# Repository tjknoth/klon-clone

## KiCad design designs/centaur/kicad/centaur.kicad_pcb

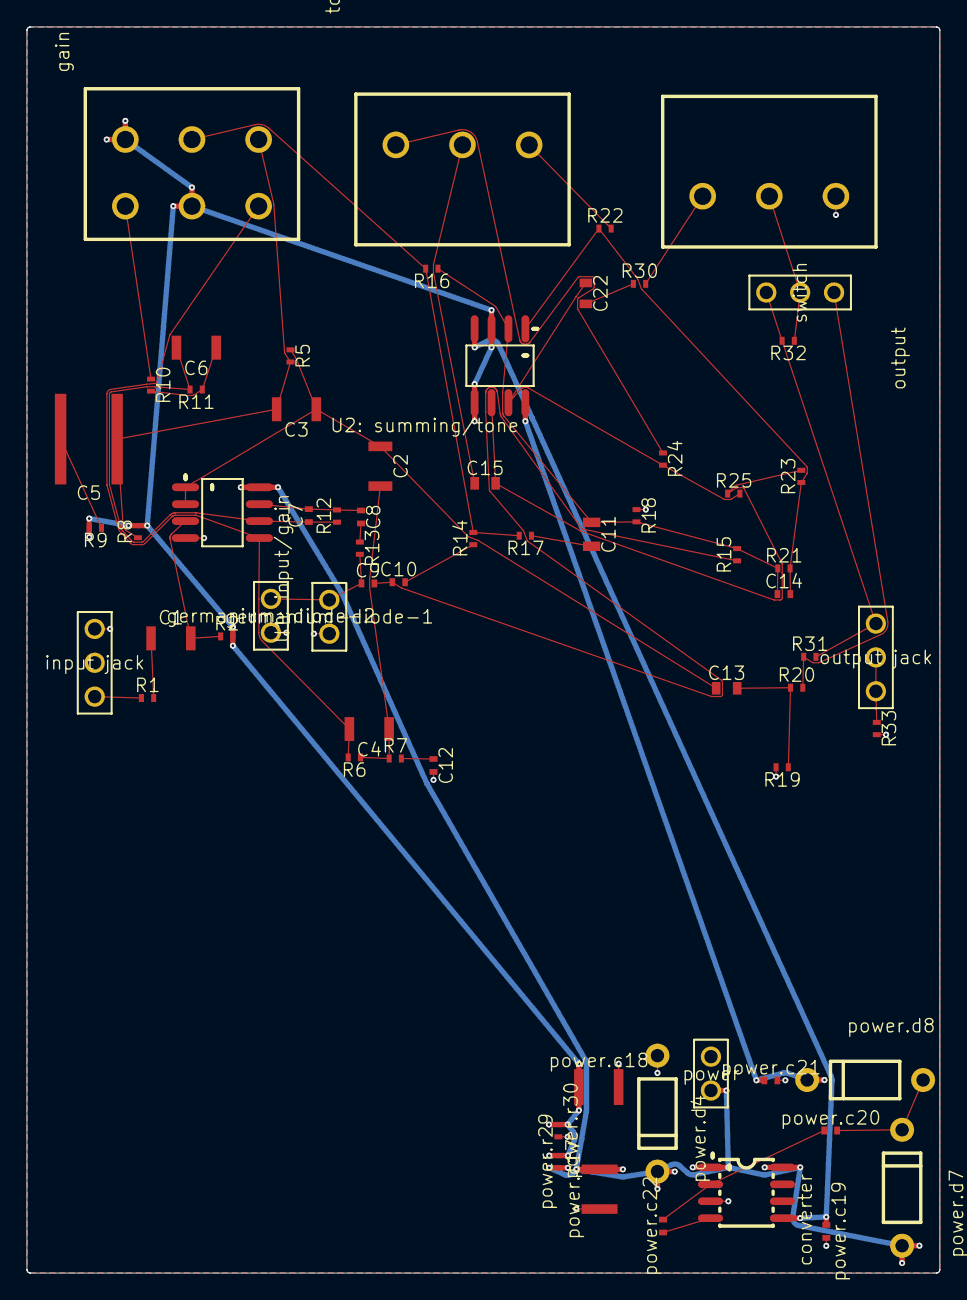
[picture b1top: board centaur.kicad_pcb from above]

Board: 2 copper layers, 68.5 x 93.5 mm, 66 parts (0 on the bottom side), 41 nets.

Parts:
C1, C2: 100n; Pkg1206
C3, C4: 68n; Pkg1206_1
C5: 390n; Pkg1825
C6: 82n; Pkg1206
C7: 390p; Pkg0402
C8, C9, C12: 1u; Pkg0402
C10: 2.2n; Pkg0402_1
C11: 27n; Pkg0805
C13, C22: 4.7u; Pkg0603
C14: 820p; Pkg0402
C15: 3.9n; Pkg0603
R1, R6: 10K; Pkg0402_3
R2: 1M; Pkg0402_3
R5: 5K1; Pkg0402_2
R7, R8: 1K5; Pkg0402_2
R9, R13: 1K; Pkg0402_3
R10: 2K; Pkg0402_4
R11, R18: 15K; Pkg0402_3
R12: 422K; Pkg0402_3
R14: 22K; Pkg0402_3
R15: 47K; Pkg0402_3
R16: 27K; Pkg0402_3
R17: 12K; Pkg0402_3
R19, R23, R25, R33: 100K; Pkg0402_3
R20, R30: 560R; Pkg0402_3
R21: 392K; Pkg0402_3
R22: 1K8; Pkg0402_3
R24: 4K7; Pkg0402_3
R31, R32: 68K; Pkg0402_3
U1: input/gain, U2: summing/tone: LP_1
converter: SO_8_L4_9_W3_9_P1_27_LS5_9_BL
gain: 10K; LP_2
germanium-diode-1, germanium-diode-2: PIN_GRID_1
input jack: PIN_GRID
output: 10K; LP
output jack: PIN_GRID
power: PIN_GRID_1
power.c17, power.c18: 47u; Pkg1210
power.c19, power.c20, power.c21, power.c22: 1u; Pkg0402
power.d4: DO_41_BD2_4_L4_7_P8_70_D0_9_FD
power.d7: DO_41_BD2_4_L4_7_P8_70_D0_9_RD_1
power.d8: DO_41_BD2_4_L4_7_P8_70_D0_9_RD
power.r29, power.r30: 27K; Pkg0402_3
switch: PIN_GRID
tone: 10K; LP

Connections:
CAP+: converter.2, power.c20.1, power.c22.2
CAP-: converter.4, power.c22.1
GND: C12.2, R18.1, R19.2, R33.2, U1: input/gain.4, converter.3, germanium-diode-1.1, germanium-diode-2.2, input jack.1, output.3, power.1, power.c17.1, power.c18.2, power.c19.2, power.c21.2, power.d4.1, power.r30.2
IN1+: C1.2, R2.1, U1: input/gain.3
IN1-: C2.1, C3.1, C13.1, R5.1, U1: input/gain.1, U1: input/gain.2
IN2+: C4.2, R6.2, U1: input/gain.5, gain.4
IN2-: C6.2, C7.1, R11.2, R12.1, U1: input/gain.6
K: power.c20.2, power.d7.1, power.d8.2
OUT1: C14.2, R21.2, R22.1, R23.1, U2: summing/tone.1
OUT2: C7.2, C8.1, R12.2, U1: input/gain.7
VCC4v5: R2.2, R8.2, R9.2, U2: summing/tone.3, U2: summing/tone.5, gain.3, gain.5, power.c18.1, power.r29.2, power.r30.1
VCC9v: U1: input/gain.8, converter.1, converter.8, power.2, power.c17.2, power.d4.2, power.d7.2, power.r29.1
VCC16v2: U2: summing/tone.8, power.c21.1, power.d8.1
VCCn8v6: U2: summing/tone.4, converter.5, power.c19.1
c2_p2: C13.2, R19.1, R20.1
c3_p2: C2.2, C4.1, R6.1, R7.1
c6_p2: C5.2, R9.1
c9_p2: C8.2, R13.1
c10_p1: C9.1, R13.2, germanium-diode-1.2, germanium-diode-2.1
c10_p2: C9.2, C10.1, R15.1
c11_p2: C10.2, R14.1
c15_p2: C22.2, R30.1
r1_p1: R1.1, input jack.3
r1_p2: C1.1, R1.2
r4_p2: R20.2, R31.1, switch.1
r7_p2: C12.1, R7.2
r10_p2: C6.1, R10.2, R11.1
r18_p1: C11.2, R17.1
r28_p1: R33.1, output jack.2, output jack.3
r243_p2: R31.2, R32.2, output jack.1, switch.3
rv-gain_p1: C3.2, C5.1, R5.2, R8.1, gain.1
rv-gain_p2: R14.2, R16.2, R17.2, gain.2
rv-gain_p6: R10.1, gain.6
rv-level_p1: R30.2, output.1
rv-level_p2: R32.1, output.2, switch.2
rv-tone_p1: R22.2, tone.1
rv-tone_p2: C15.1, tone.2
rv-tone_p3: R24.1, tone.3
u2_IN1-: C11.1, C14.1, R15.2, R16.1, R18.2, R21.1, U2: summing/tone.2
u2_IN2-: C15.2, R23.2, R25.1, U2: summing/tone.6
u2_OUT2: C22.1, R24.2, R25.2, U2: summing/tone.7

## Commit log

2023-09-05 init
2023-09-06 power module stuff
2023-09-06 a bunch of stuff
2023-09-06 power circuit?
2023-09-06 schematic bug
2023-09-07 output circuit, panel-mount headers
2023-09-09 circuit done?
2023-09-12 add designs, working commit for schematic bug
2023-09-12 progress?
2023-09-12 got it right?
2023-09-13 remove backups
2023-09-13 dual gang
2023-09-14 routed
2023-09-14 some labels
2023-09-15 labels and slightly cleaner placement
2023-09-15 slight shift
2023-09-15 layout, remove kicad from git
2023-11-20 reset everything
2023-11-20 real reset
2023-11-20 got it routed sorta
2023-11-20 routed better
2023-11-21 touched up
2023-11-21 via updates, pours, placements, etc
2023-11-21 labels
2023-11-21 lookin nice
2023-11-21 cleanup code
2023-11-22 random stuff
2023-11-22 bug state
2023-11-22 db cache
2024-01-24 new version, still segfaults
2024-10-23 reset designs folder
2024-10-24 schemnatic update, small net bugfix
2024-10-25 everything is on board
2024-10-25 new component, new placements
2024-10-25 power placement:
2024-10-25 move stuff, bigger soldermask, etc
2024-10-25 designs
2024-10-25 some routing and stuff
2024-10-25 routed wow
2024-10-25 fat ass traces
2024-10-26 finished routing
2024-10-28 code and net updates
2024-10-28 partway done redoing
2024-10-28 ready to expand pads
2024-10-29 working commit - towards auto pad transformation, added test points
2024-10-29 working commit
2024-10-29 gnd and 9v routed
2024-10-30 a pretty good state
2024-10-31 this one might be ok
2024-10-31 this is pretty good
2024-11-01 good 2 go
